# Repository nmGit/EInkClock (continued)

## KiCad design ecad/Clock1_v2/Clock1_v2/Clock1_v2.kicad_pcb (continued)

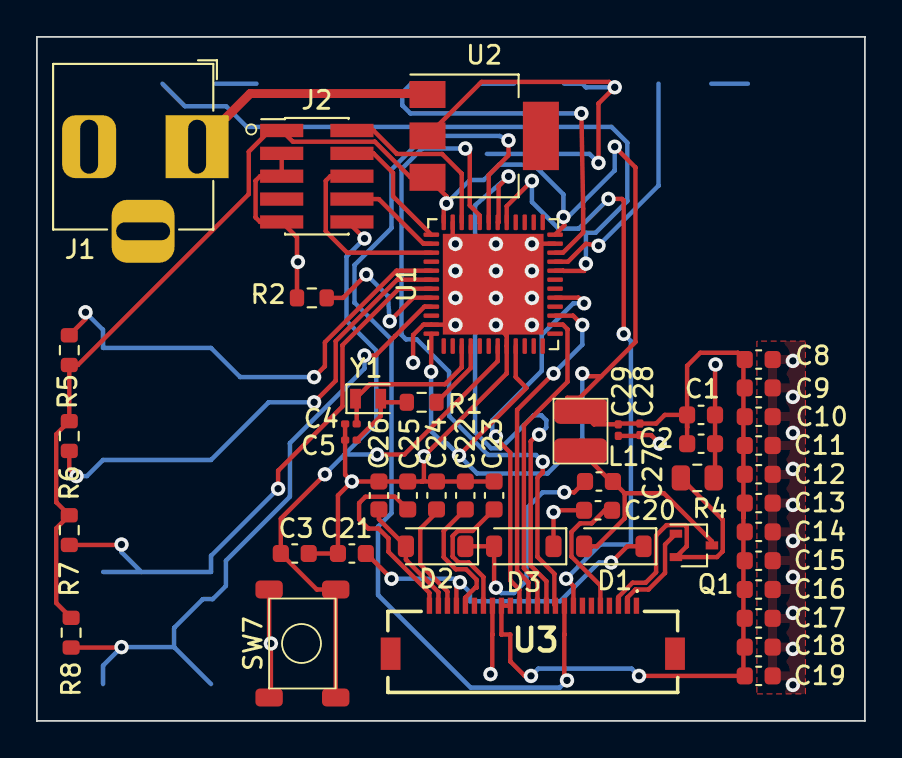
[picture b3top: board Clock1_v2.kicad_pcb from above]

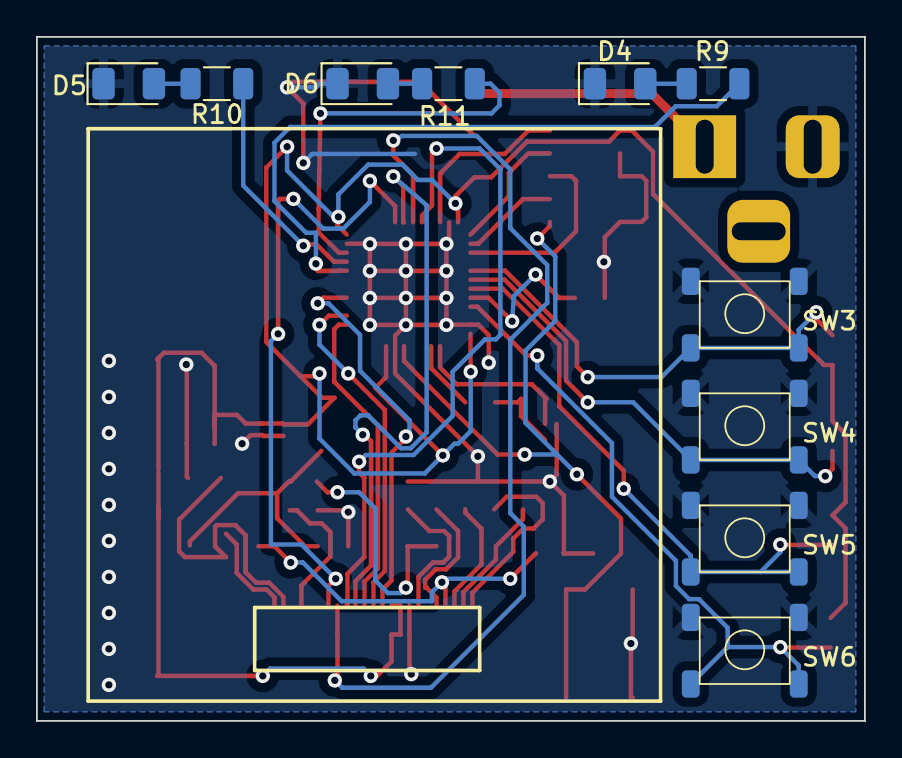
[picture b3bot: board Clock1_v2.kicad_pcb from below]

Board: 2 copper layers, 46.0 x 38.0 mm, 56 parts (10 on the bottom side), 40 nets.

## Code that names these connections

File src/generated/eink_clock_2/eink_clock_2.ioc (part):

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Mcu.Name=STM32F103C(8-B)Tx
Mcu.Package=LQFP48
Mcu.UserName=STM32F103C8Tx
PA0-WKUP.GPIOParameters=GPIO_Label
PA0-WKUP.GPIO_Label=WAKEUP
PA0-WKUP.Signal=GPIO_Input
PA1.GPIOParameters=GPIO_Label
PA1.GPIO_Label=BTN_DOWN
PA1.Signal=GPIO_Input
PA10.GPIOParameters=GPIO_PuPd,GPIO_Label
PA10.GPIO_Label=EPD_NBUSY
PA10.GPIO_PuPd=GPIO_PULLUP
PA10.Signal=GPIO_Input
PA11.Mode=Device
PA11.Signal=USB_DM
PA12.Mode=Device
PA12.Signal=USB_DP
PA4.Mode=NSS_Signal_Hard_Output
PA4.Signal=SPI1_NSS
PA5.Mode=Simplex_Bidirectional_Master
PA5.Signal=SPI1_SCK
PA7.Mode=Simplex_Bidirectional_Master
PA7.Signal=SPI1_MOSI
PA8.GPIOParameters=GPIO_Label
PA8.GPIO_Label=EPD_BS
PA8.Signal=GPIO_Output
PA9.GPIOParameters=GPIO_Label
PA9.GPIO_Label=EPD_DC
PA9.Signal=GPIO_Output
PB12.GPIOParameters=GPIO_Label
PB12.GPIO_Label=BTN_UP
PB12.Signal=GPIO_Input
PB15.GPIOParameters=GPIO_PuPd,GPIO_Label
PB15.GPIO_Label=EPD_NRESET
PB15.GPIO_PuPd=GPIO_PULLUP
PB15.Signal=GPIO_Output
PC14-OSC32_IN.Mode=LSE-External-Oscillator
PC14-OSC32_IN.Signal=RCC_OSC32_IN
PC15-OSC32_OUT.Mode=LSE-External-Oscillator
PC15-OSC32_OUT.Signal=RCC_OSC32_OUT
RCC.SYSCLKFreq_VALUE=48000000
RCC.SYSCLKSource=RCC_SYSCLKSOURCE_PLLCLK
board=custom

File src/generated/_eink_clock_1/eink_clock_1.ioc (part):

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Mcu.Name=STM32F103CBUx
Mcu.Package=UFQFPN48
Mcu.UserName=STM32F103CBUx
PA10.GPIOParameters=GPIO_PuPd,GPIO_Label
PA10.GPIO_Label=EPD_NBUSY
PA10.GPIO_PuPd=GPIO_PULLUP
PA10.Signal=GPIO_Input
PA11.GPIOParameters=GPIO_Label
PA11.GPIO_Label=EPD_NRESET
PA11.Signal=GPIO_Output
PA4.Mode=NSS_Signal_Hard_Output
PA4.Signal=SPI1_NSS
PA5.Mode=Simplex_Bidirectional_Master
PA5.Signal=SPI1_SCK
PA7.Mode=Simplex_Bidirectional_Master
PA7.Signal=SPI1_MOSI
PA8.GPIOParameters=PinState,GPIO_Label
PA8.GPIO_Label=EPD_BS
PA8.PinState=GPIO_PIN_RESET
PA8.Signal=GPIO_Output
PA9.GPIOParameters=PinState,GPIO_Label
PA9.GPIO_Label=EPD_DC
PA9.PinState=GPIO_PIN_RESET
PA9.Signal=GPIO_Output
PB10.GPIOParameters=PinState,GPIO_Label,GPIO_ModeDefaultOutputPP
PB10.GPIO_Label=LED2
PB10.GPIO_ModeDefaultOutputPP=GPIO_MODE_OUTPUT_PP
PB10.PinState=GPIO_PIN_SET
PB10.Signal=GPIO_Output
PB11.GPIOParameters=PinState,GPIO_Label,GPIO_ModeDefaultOutputPP
PB11.GPIO_Label=LED3
PB11.GPIO_ModeDefaultOutputPP=GPIO_MODE_OUTPUT_PP
PB11.PinState=GPIO_PIN_SET
PB11.Signal=GPIO_Output
PB2.GPIOParameters=PinState,GPIO_Label,GPIO_ModeDefaultOutputPP
PB2.GPIO_Label=LED1
PB2.GPIO_ModeDefaultOutputPP=GPIO_MODE_OUTPUT_PP
PB2.PinState=GPIO_PIN_SET
PB2.Signal=GPIO_Output
RCC.SYSCLKFreq_VALUE=64000000
RCC.SYSCLKSource=RCC_SYSCLKSOURCE_PLLCLK
board=custom

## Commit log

2024-07-06 Submodule
